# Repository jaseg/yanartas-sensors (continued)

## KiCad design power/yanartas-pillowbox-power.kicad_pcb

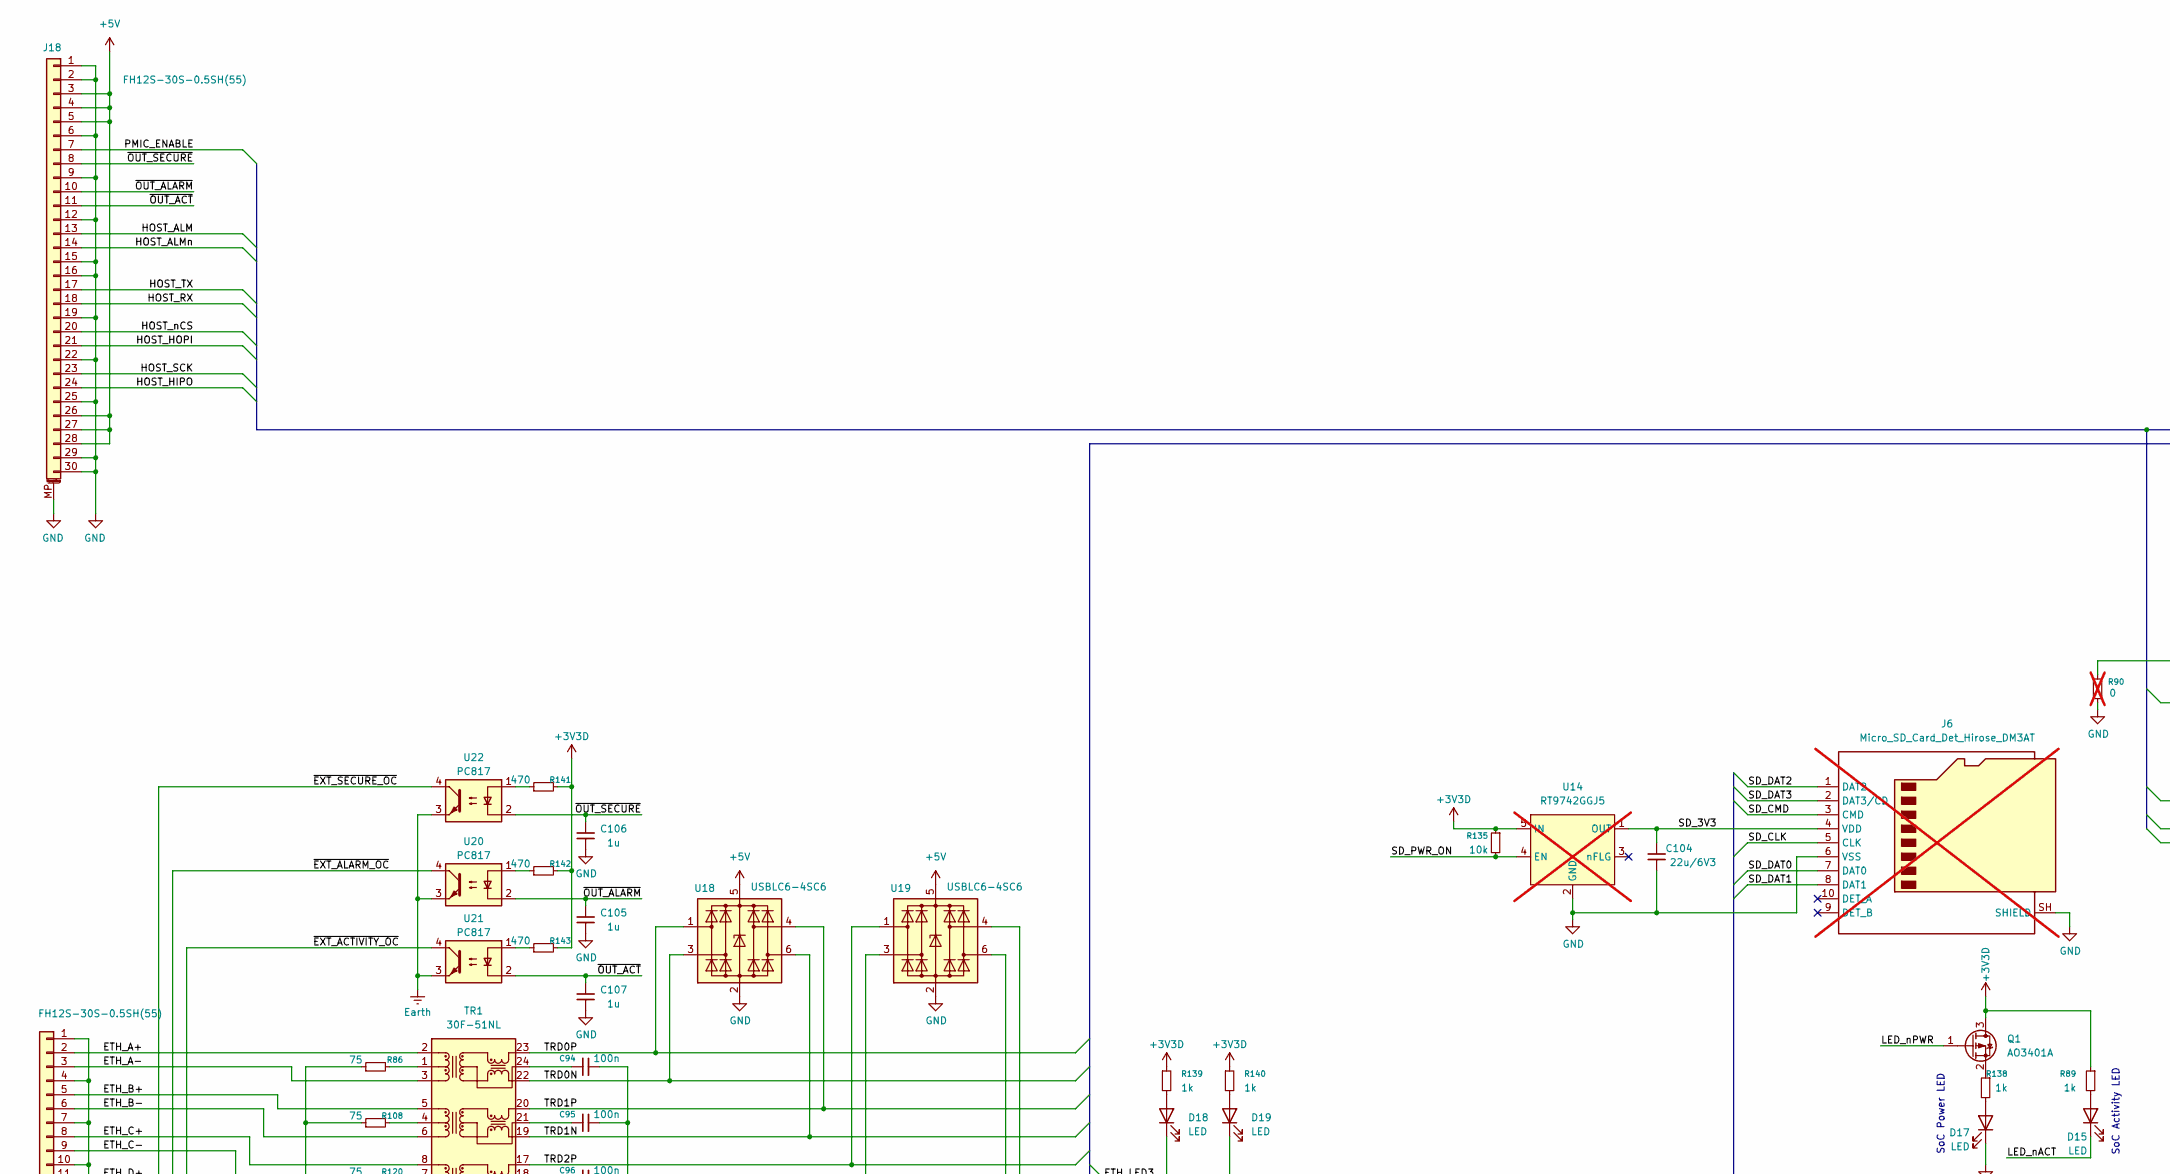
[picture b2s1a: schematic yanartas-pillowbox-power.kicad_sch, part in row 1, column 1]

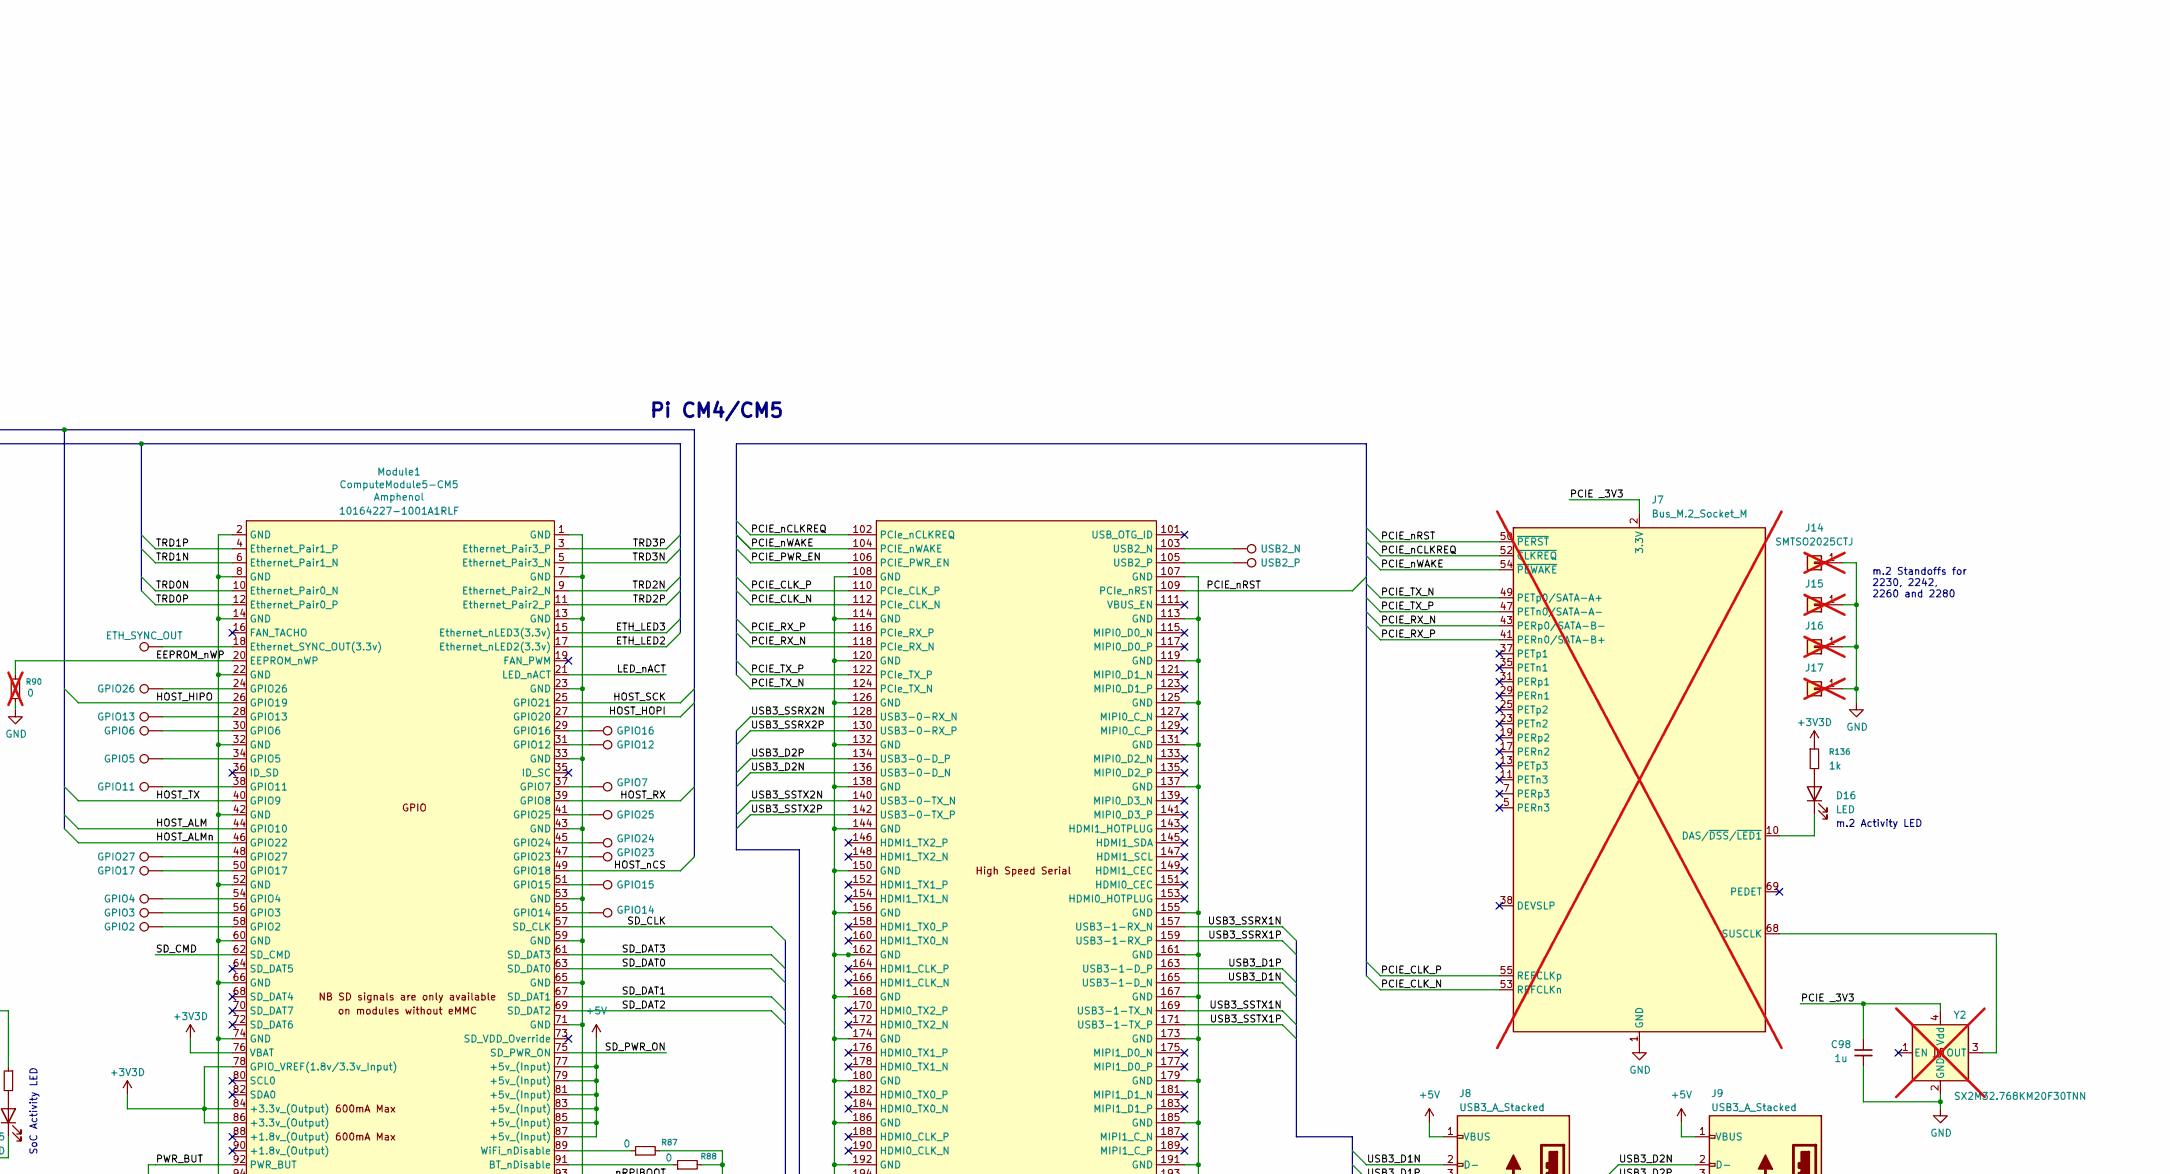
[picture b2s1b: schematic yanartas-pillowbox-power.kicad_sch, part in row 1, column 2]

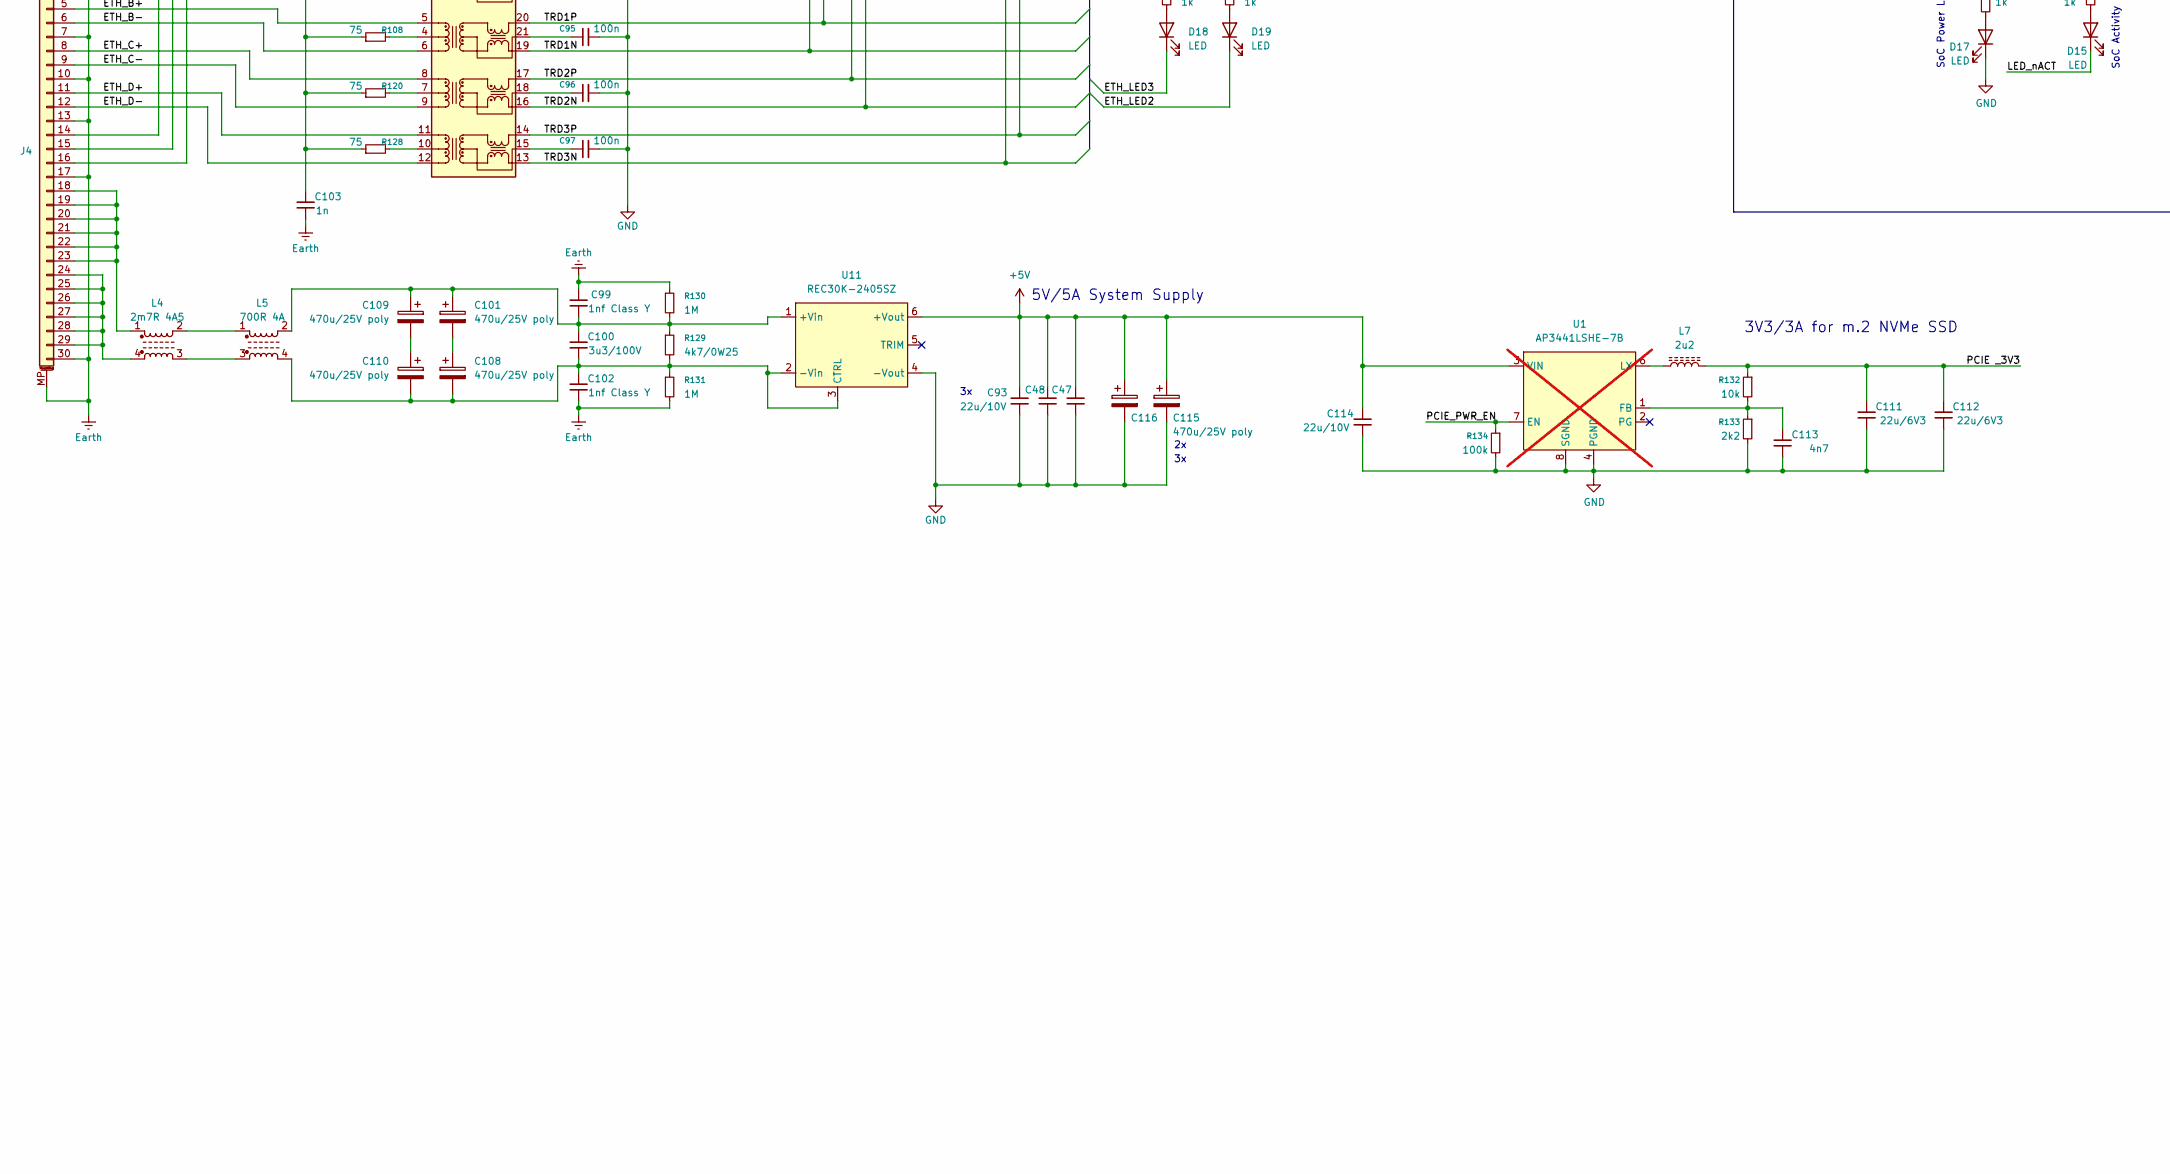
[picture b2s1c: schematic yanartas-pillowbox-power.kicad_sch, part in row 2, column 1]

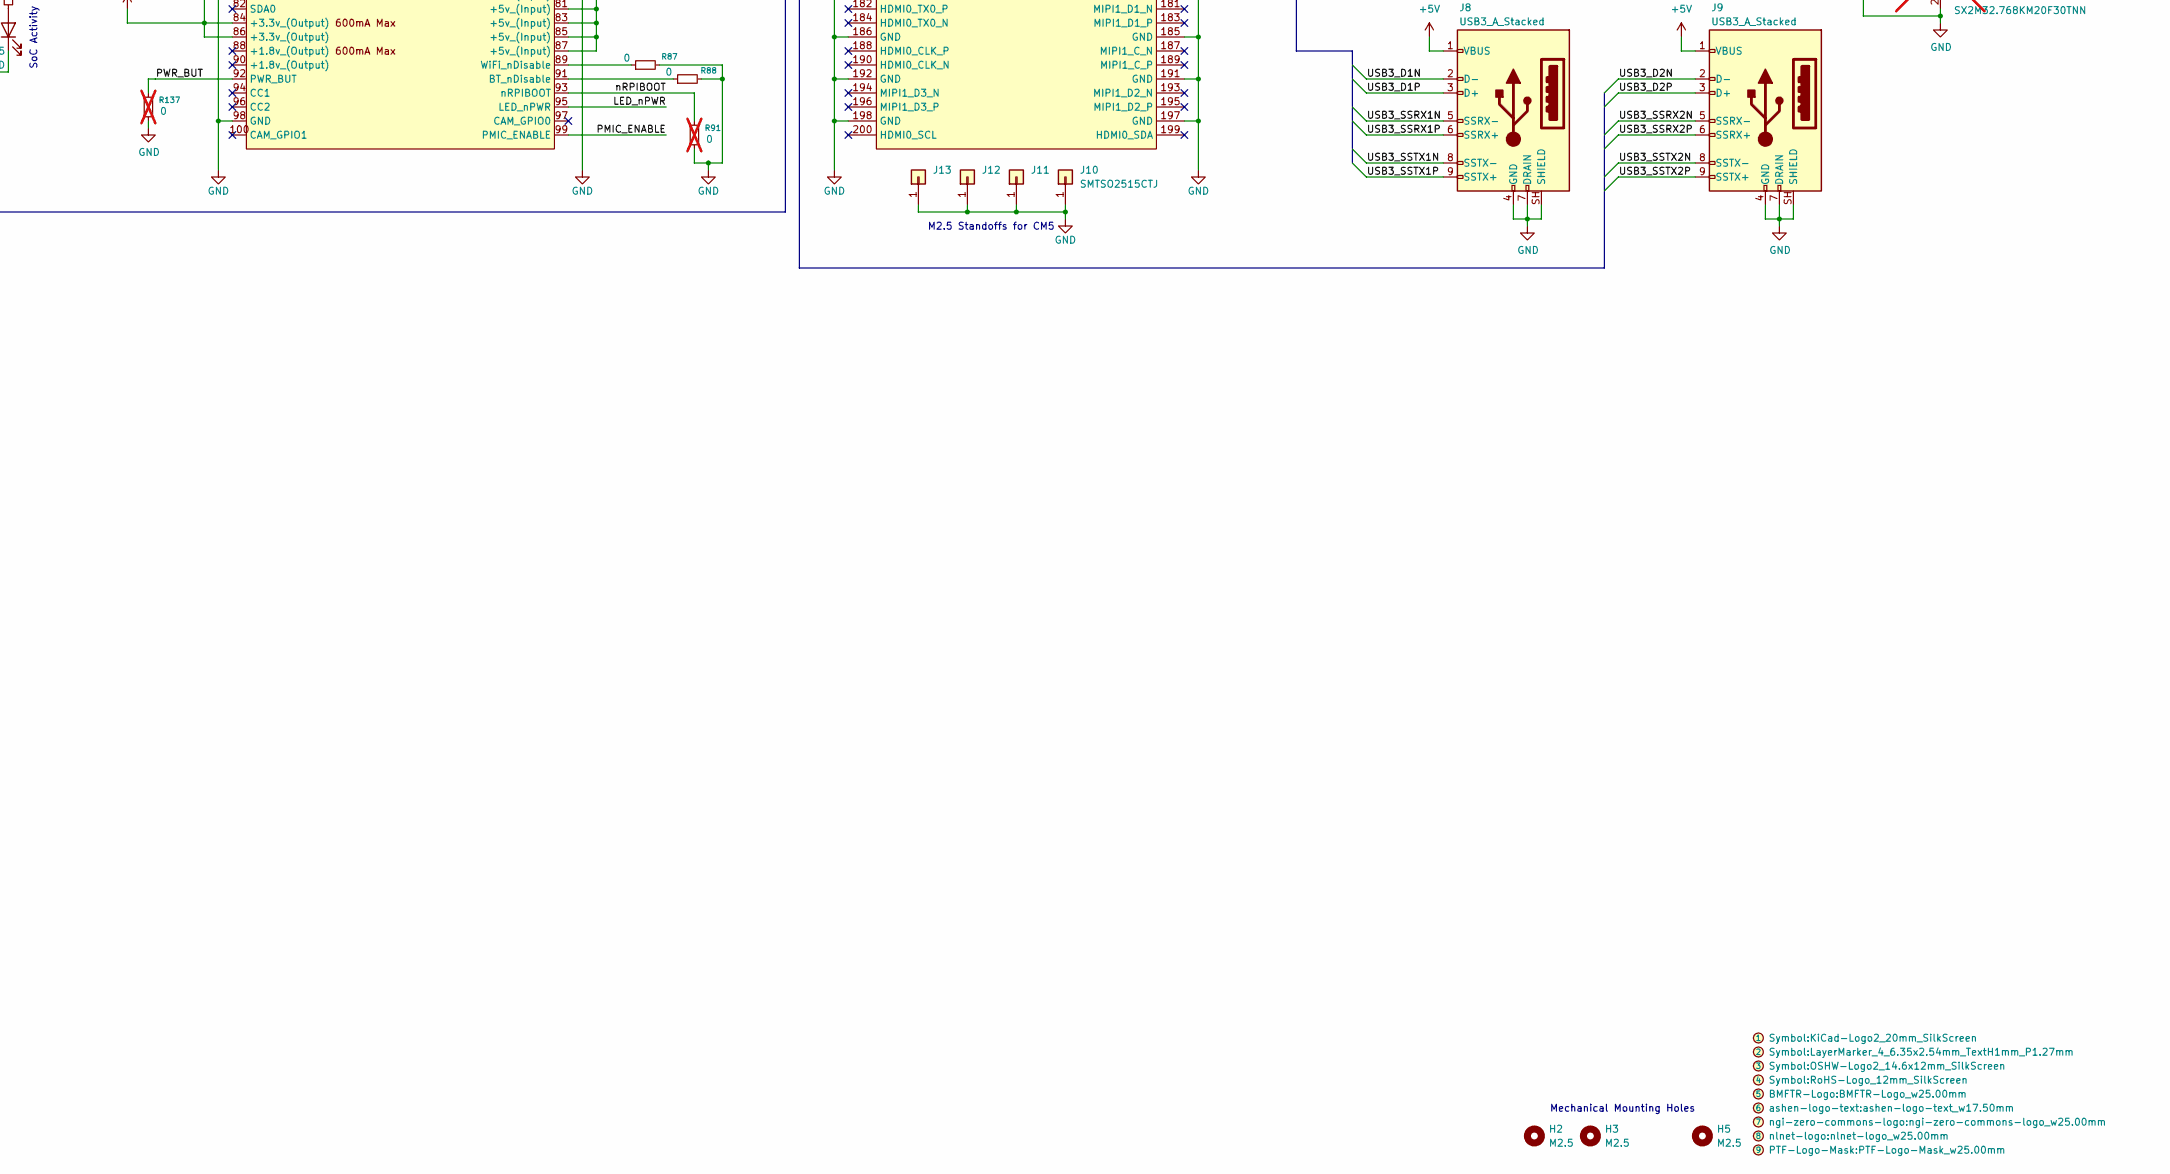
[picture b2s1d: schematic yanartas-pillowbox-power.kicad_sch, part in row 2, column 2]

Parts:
C47, C48, C93, C114: 22u/10V; C_0805_2012Metric; LCSC C45783
C94, C95, C96, C97: 100n; C_0402_1005Metric; LCSC C1525
C98, C105, C106, C107: 1u; C_0402_1005Metric; LCSC C52923
C99, C102: 1nf Class Y; C_Rect_L13.0mm_W4.0mm_P10.00mm_FKS3_FKP3_MKS4; LCSC C361361
C100: 3u3/100V; C_1206_3216Metric; LCSC C695361
C101, C108, C109, C110, C115, C116: 470u/25V poly; CP_Radial_D10.0mm_P5.00mm; MfgPN A750MS477M1EAAE015; LCSC C696345
C103: 1n; C_0603_1608Metric; LCSC C1588
C104, C111, C112: 22u/6V3; C_0805_2012Metric; LCSC C45783
C113: 4n7; C_0402_1005Metric; LCSC C1538
D15, D16, D17, D18, D19: LED; LED_0603_1608Metric; LCSC C2290
H2, H3, H5: M2.5; MountingHole_2.7mm_M2.5; LCSC NA
J4, J18: FH12S-30S-0.5SH(55); Hirose_FH12-30S-0.5SH_1x30-1MP_P0.50mm_Horizontal; LCSC C3169607
J6: Micro_SD_Card_Det_Hirose_DM3AT; microSD_HC_Hirose_DM3AT-SF-PEJM5; MPN DM3AT-SF-PEJM5; LCSC C114218; not fitted
J7: Bus_M.2_Socket_M; CONN-SMD_MDT420M02001; LCSC C2927698; not fitted
J8, J9: USB3_A_Stacked; USB_A_Receptacle_XKB_U231-091N-4BLRA00-S; LCSC C2880618
J10, J11, J12, J13: SMTSO2515CTJ; SINHOO_SMTSO25XX; LCSC C2915629
J14, J15, J16, J17: SMTSO2025CTJ; SINHOO_SMTSO20XX; LCSC C2916321; not fitted
L4: 2m7R 4A5; EPCOS_B82723A; MPN B82723A2402N001; LCSC NA
L5: 700R 4A; TDK_ACM7060; MPN ACM7060-701-2PL-TL01; LCSC C78246
L7: 2u2; CJIANG_FXL0420; LCSC C167206
Module1: ComputeModule5-CM5; Raspberry-Pi-5-Compute-Module-A; Part Description 100 Position Connector Receptacle, Cent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; LCSC C6782225
Module2: ComputeModule5-CM5; Raspberry-Pi-5-Compute-Module-B; Part Description 100 Position Connector Receptacle, Cent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; LCSC C6782225
Q1: AO3401A; SOT-23; LCSC C15127
R86, R108, R120, R128: 75; R_0402_1005Metric; LCSC C25133
R87, R88: 0; R_0402_1005Metric; LCSC C17168
R89, R136, R138, R139, R140: 1k; R_0402_1005Metric; LCSC C11702
R90, R91, R137: 0; R_0402_1005Metric; LCSC C17168; not fitted
R129: 4k7/0W25; R_1206_3216Metric; LCSC C17936
R130, R131: 1M; R_0603_1608Metric; LCSC C22935
R132, R135: 10k; R_0402_1005Metric; LCSC C25744
R133: 2k2; R_0402_1005Metric; LCSC C25879
R134: 100k; R_0402_1005Metric; LCSC C25741
R141, R142, R143: 470; R_0402_1005Metric; LCSC C25117
TP1: GPIO27; TestPoint_Pad_D1.0mm; LCSC NA
TP2: GPIO17; TestPoint_Pad_D1.0mm; LCSC NA
TP3: GPIO4; TestPoint_Pad_D1.0mm; LCSC NA
TP4: GPIO3; TestPoint_Pad_D1.0mm; LCSC NA
TP5: GPIO2; TestPoint_Pad_D1.0mm; LCSC NA
TP6: GPIO11; TestPoint_Pad_D1.0mm; LCSC NA
TP7: GPIO5; TestPoint_Pad_D1.0mm; LCSC NA
TP8: GPIO6; TestPoint_Pad_D1.0mm; LCSC NA
TP9: GPIO13; TestPoint_Pad_D1.0mm; LCSC NA
TP10: GPIO26; TestPoint_Pad_D1.0mm; LCSC NA
TP11: ETH_SYNC_OUT; TestPoint_Pad_D1.0mm; LCSC NA
TP12: GPIO14; TestPoint_Pad_D1.0mm; LCSC NA
TP13: GPIO15; TestPoint_Pad_D1.0mm; LCSC NA
TP14: GPIO23; TestPoint_Pad_D1.0mm; LCSC NA
TP15: GPIO24; TestPoint_Pad_D1.0mm; LCSC NA
TP16: GPIO25; TestPoint_Pad_D1.0mm; LCSC NA
TP17: GPIO7; TestPoint_Pad_D1.0mm; LCSC NA
TP18: GPIO12; TestPoint_Pad_D1.0mm; LCSC NA
TP19: GPIO16; TestPoint_Pad_D1.0mm; LCSC NA
TP20: USB2_N; TestPoint_Pad_D1.0mm; LCSC NA
TP21: USB2_P; TestPoint_Pad_D1.0mm; LCSC NA
TR1: 30F-51NL; Transformer_Ethernet_YDS_30F-51NL_SO-24_7.1x15.1mm; LCSC C123168
U1: AP3441LSHE-7B; DFN-8-1EP_2x2mm_P0.5mm_EP1.05x1.75mm; LCSC C2072094; not fitted
U11: REC30K-2405SZ; RECOM_REC30K-2405SZ; LCSC NA
U14: RT9742GGJ5; SOT-23-5; Part Description Power Switch/Driver 1:1 N-Channel 1A TS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; LCSC C250547; not fitted
U18, U19: USBLC6-4SC6; SOT-23-6; LCSC C558419
U20, U21, U22: PC817; SMDIP-4_W7.62mm; LCSC C41807
Y2: SX2M32.768KM20F30TNN; Crystal_SMD_2520-4Pin_2.5x2.0mm; LCSC C2901603; not fitted

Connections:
+5V: C47.2, C48.2, C93.2, C114.2, C115.1, C116.1, J8.1 (VBUS), J9.1 (VBUS), J18.3, J18.4, J18.5, J18.26, J18.27, J18.28, Module1.77 (+5v_(Input)), Module1.79 (+5v_(Input)), Module1.81 (+5v_(Input)), Module1.83 (+5v_(Input)), Module1.85 (+5v_(Input)), Module1.87 (+5v_(Input)), U1.3 (VIN), U11.6 (+Vout), U18.5 (VBUS), U19.5 (VBUS)
/EEPROM_nWP: Module1.20 (EEPROM_nWP), R90.2
/ETH_A+: J4.2, TR1.2 (TD1+)
/ETH_A-: J4.3, TR1.3 (TD1-)
/ETH_B+: J4.5, TR1.5 (TD2+)
/ETH_B-: J4.6, TR1.6 (TD2-)
/ETH_C+: J4.8, TR1.8 (TD3+)
/ETH_C-: J4.9, TR1.9 (TD3-)
/ETH_D+: J4.11, TR1.11 (TD4+)
/ETH_D-: J4.12, TR1.12 (TD4-)
/ETH_LED2: D19.1 (K), Module1.17 (Ethernet_nLED2(3.3v))
/ETH_LED3: D18.1 (K), Module1.15 (Ethernet_nLED3(3.3v))
/HOST_ALM: J18.13, Module1.44 (GPIO10)
/HOST_ALMn: J18.14, Module1.46 (GPIO22)
/HOST_HIPO: J18.24, Module1.26 (GPIO19)
/HOST_HOPI: J18.21, Module1.27 (GPIO20)
/HOST_RX: J18.18, Module1.39 (GPIO8)
/HOST_SCK: J18.23, Module1.25 (GPIO21)
/HOST_TX: J18.17, Module1.40 (GPIO9)
/HOST_nCS: J18.20, Module1.49 (GPIO18)
/PCIE _3V3: C98.2, C111.2, C112.2, J7.2 (3.3V), J7.4 (3.3V), J7.12 (3.3V), J7.14 (3.3V), J7.16 (3.3V), J7.18 (3.3V), J7.70 (3.3V), J7.72 (3.3V), J7.74 (3.3V), L7.2, R132.1, Y2.4 (Vdd)
/PCIE_CLK_N: J7.53 (REFCLKn), Module2.112 (PCIe_CLK_N)
/PCIE_CLK_P: J7.55 (REFCLKp), Module2.110 (PCIe_CLK_P)
/PCIE_PWR_EN: Module2.106 (PCIE_PWR_EN), R134.1, U1.7 (EN)
/PCIE_RX_N: J7.43 (PERp0/SATA-B-), Module2.118 (PCIe_RX_N)
/PCIE_RX_P: J7.41 (PERn0/SATA-B+), Module2.116 (PCIe_RX_P)
/PCIE_TX_N: J7.49 (PETp0/SATA-A+), Module2.124 (PCIe_TX_N)
/PCIE_TX_P: J7.47 (PETn0/SATA-A-), Module2.122 (PCIe_TX_P)
/PCIE_nCLKREQ: J7.52 (~CLKREQ), Module2.102 (PCIe_nCLKREQ)
/PCIE_nRST: J7.50 (~PERST), Module2.109 (PCIe_nRST)
/PCIE_nWAKE: J7.54 (~PEWAKE), Module2.104 (PCIE_nWAKE)
/PMIC_ENABLE: J18.7, Module1.99 (PMIC_ENABLE)
/PWR_BUT: Module1.92 (PWR_BUT), R137.2
/SD_3V3: C104.2, J6.4 (VDD), U14.1 (OUT)
/SD_CLK: J6.5 (CLK), Module1.57 (SD_CLK)
/SD_CMD: J6.3 (CMD), Module1.62 (SD_CMD)
/SD_DAT0: J6.7 (DAT0), Module1.63 (SD_DAT0)
/SD_DAT1: J6.8 (DAT1), Module1.67 (SD_DAT1)
/SD_DAT2: J6.1 (DAT2), Module1.69 (SD_DAT2)
/SD_DAT3: J6.2 (DAT3/CD), Module1.61 (SD_DAT3)
/SD_PWR_ON: Module1.75 (SD_PWR_ON), R135.2, U14.4 (EN)
/TRD0N: Module1.10 (Ethernet_Pair0_N), TR1.22 (MX1-), U18.3 (I/O2)
/TRD0P: Module1.12 (Ethernet_Pair0_P), TR1.23 (MX1+), U18.1 (I/O1)
/TRD1N: Module1.6 (Ethernet_Pair1_N), TR1.19 (MX2-), U18.6 (I/O4)
/TRD1P: Module1.4 (Ethernet_Pair1_P), TR1.20 (MX2+), U18.4 (I/O3)
/TRD2N: Module1.9 (Ethernet_Pair2_N), TR1.16 (MX3-), U19.3 (I/O2)
/TRD2P: Module1.11 (Ethernet_Pair2_P), TR1.17 (MX3+), U19.1 (I/O1)
/TRD3N: Module1.5 (Ethernet_Pair3_N), TR1.13 (MX4-), U19.6 (I/O4)
/TRD3P: Module1.3 (Ethernet_Pair3_P), TR1.14 (MX4+), U19.4 (I/O3)
/USB3_D1N: J8.2 (D-), Module2.165 (USB3-1-D_N)
/USB3_D1P: J8.3 (D+), Module2.163 (USB3-1-D_P)
/USB3_D2N: J9.2 (D-), Module2.136 (USB3-0-D_N)
/USB3_D2P: J9.3 (D+), Module2.134 (USB3-0-D_P)
/USB3_SSRX1N: J8.5 (SSRX-), Module2.157 (USB3-1-RX_N)
/USB3_SSRX1P: J8.6 (SSRX+), Module2.159 (USB3-1-RX_P)
/USB3_SSRX2N: J9.5 (SSRX-), Module2.128 (USB3-0-RX_N)
/USB3_SSRX2P: J9.6 (SSRX+), Module2.130 (USB3-0-RX_P)
/USB3_SSTX1N: J8.8 (SSTX-), Module2.169 (USB3-1-TX_N)
/USB3_SSTX1P: J8.9 (SSTX+), Module2.171 (USB3-1-TX_P)
/USB3_SSTX2N: J9.8 (SSTX-), Module2.140 (USB3-0-TX_N)
/USB3_SSTX2P: J9.9 (SSTX+), Module2.142 (USB3-0-TX_P)
/nRPIBOOT: Module1.93 (nRPIBOOT), R91.2
/~EXT_ACTIVITY_OC: J4.16, U21.4
/~EXT_ALARM_OC: J4.15, U20.4
/~EXT_SECURE_OC: J4.14, U22.4
/~OUT_ACT: C107.2, J18.11, U21.2
/~OUT_ALARM: C105.2, J18.10, U20.2
/~OUT_SECURE: C106.2, J18.8, U22.2
unnamed: C94.1, TR1.24 (CT)
unnamed: C95.1, TR1.21 (CT)
unnamed: C96.1, TR1.18 (CT)
unnamed: C97.1, TR1.15 (CT)
unnamed: C101.2, C108.1
unnamed: C103.2, R86.1, R108.1, R120.1, R128.1
unnamed: C109.2, C110.1
unnamed: D15.2 (A), R89.2
unnamed: D16.2 (A), R136.2
unnamed: D16.1 (K), J7.10 (DAS/~DSS/~LED1)
unnamed: D17.2 (A), R138.2
unnamed: D18.2 (A), R139.2
unnamed: D19.2 (A), R140.2
unnamed: J7.68 (SUSCLK), Y2.3 (OUT)
unnamed: L4.2, L5.1
unnamed: L4.3, L5.3
unnamed: Module1.91 (BT_nDisable), R88.1
unnamed: Module1.18 (Ethernet_SYNC_OUT(3.3v)), TP11.1 (1_1)
unnamed: Module1.58 (GPIO2), TP5.1 (1_1)
unnamed: Module1.56 (GPIO3), TP4.1 (1_1)
unnamed: Module1.54 (GPIO4), TP3.1 (1_1)
unnamed: Module1.34 (GPIO5), TP7.1 (1_1)
unnamed: Module1.30 (GPIO6), TP8.1 (1_1)
unnamed: Module1.37 (GPIO7), TP17.1 (1_1)
unnamed: Module1.38 (GPIO11), TP6.1 (1_1)
unnamed: Module1.31 (GPIO12), TP18.1 (1_1)
unnamed: Module1.28 (GPIO13), TP9.1 (1_1)
unnamed: Module1.55 (GPIO14), TP12.1 (1_1)
unnamed: Module1.51 (GPIO15), TP13.1 (1_1)
unnamed: Module1.29 (GPIO16), TP19.1 (1_1)
unnamed: Module1.50 (GPIO17), TP2.1 (1_1)
unnamed: Module1.47 (GPIO23), TP14.1 (1_1)
unnamed: Module1.45 (GPIO24), TP15.1 (1_1)
unnamed: Module1.41 (GPIO25), TP16.1 (1_1)
unnamed: Module1.24 (GPIO26), TP10.1 (1_1)
unnamed: Module1.48 (GPIO27), TP1.1 (1_1)
unnamed: Module1.89 (WiFi_nDisable), R87.1
unnamed: Module2.103 (USB2_N), TP20.1 (1_1)
unnamed: Module2.105 (USB2_P), TP21.1 (1_1)
unnamed: R86.2, TR1.1 (CT)
unnamed: R108.2, TR1.4 (CT)
unnamed: R120.2, TR1.7 (CT)
unnamed: R128.2, TR1.10 (CT)
unnamed: R141.1, U22.1
unnamed: R142.1, U20.1
unnamed: R143.1, U21.1
unnamed: C113.2, R132.2, R133.1, U1.1 (FB)
unnamed: L7.1, U1.6 (LX)
unnamed: C99.1, C100.2, C101.1, C109.1, L5.2, R129.1, R130.2, U11.1 (+Vin)
unnamed: C100.1, C102.2, C108.2, C110.2, L5.4, R129.2, R131.1, U11.2 (-Vin), U11.3 (CTRL)

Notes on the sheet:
m.2 Standoffs for 2230, 2242, 2260 and 2280
SoC Power LED
SoC Activity LED
Pi CM4/CM5
M2.5 Standoffs for CM5
5V/5A System Supply
Mechanical Mounting Holes
m.2 Activity LED
3V3/3A for m.2 NVMe SSD

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
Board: 6 copper layers, 107 parts (6 on the bottom side), 117 nets, no tracks yet.
